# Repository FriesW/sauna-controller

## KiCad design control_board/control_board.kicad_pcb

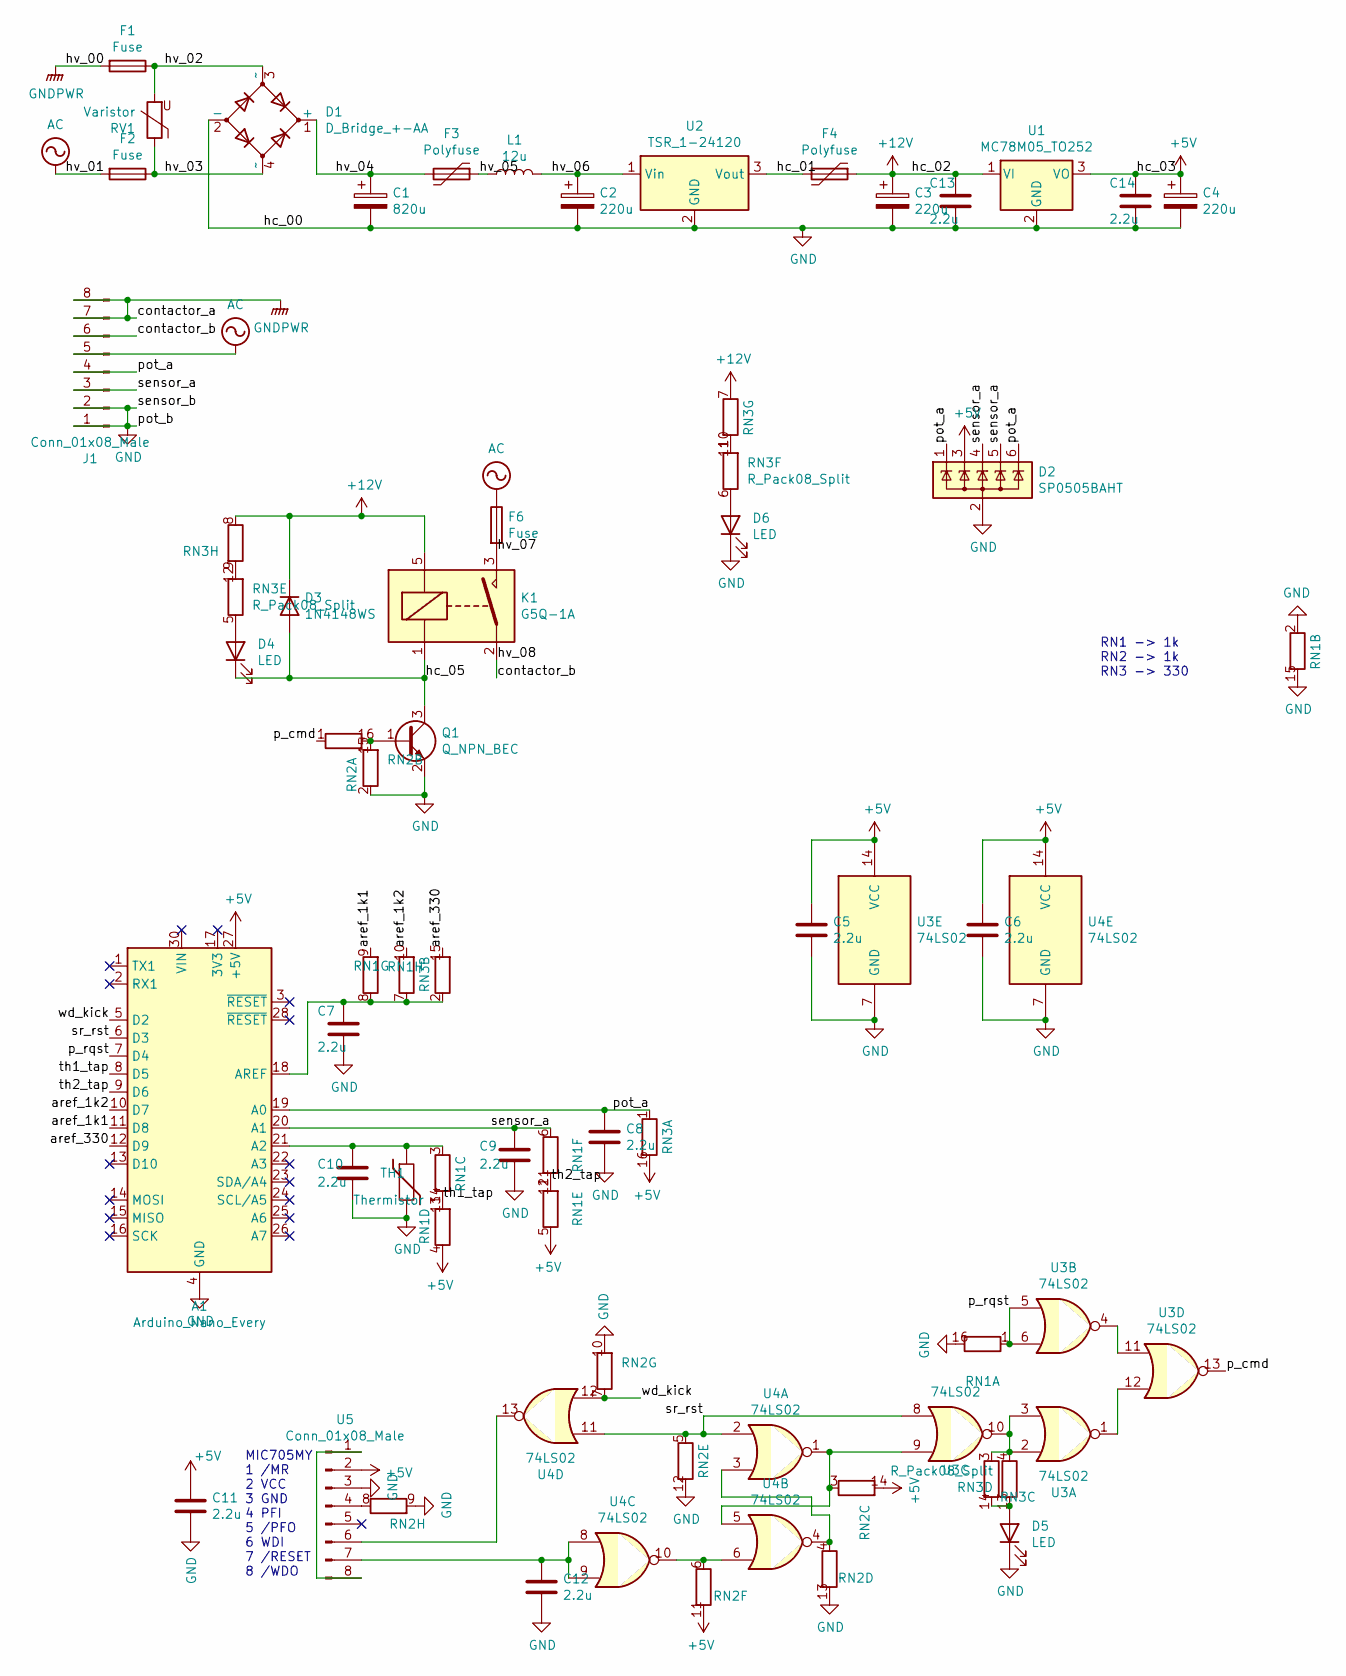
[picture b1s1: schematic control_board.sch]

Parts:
A1: Arduino_Nano_Every; Arduino_Nano
C1: 820u; CP_Elec_16x17.5
C2, C3, C4: 220u; CP_Elec_10x10
C5, C6, C7, C8, C9, C10, C11, C12, C13, C14: 2.2u; C_0805_2012Metric_Pad1.18x1.45mm_HandSolder
D1: D_Bridge_+-AA; Diode_Bridge_Diotec_ABS
D2: SP0505BAHT; SOT-23-6_Handsoldering
D3: 1N4148WS; D_SOD-323_HandSoldering
D4, D5, D6: LED; LED_0805_2012Metric_Pad1.15x1.40mm_HandSolder
F1, F2: Fuse; R_Axial_DIN0411_L9.9mm_D3.6mm_P12.70mm_Horizontal
F3, F4: Polyfuse; Fuse_2920_7451Metric_Pad2.10x5.45mm_HandSolder
F6: Fuse; Fuse_Littelfuse_395Series
J1: Conn_01x08_Male; JST_VH_B8P-VH_1x08_P3.96mm_Vertical
K1: G5Q-1A; Relay_SPDT_Omron-G5Q-1
L1: 12u; L_Abracon_ASPI-0630LR
Q1: Q_NPN_BEC; SOT-23_Handsoldering
RN1, RN2, RN3: R_Pack08_Split; SOIC-16_4.55x10.3mm_P1.27mm
RV1: Varistor; RV_Disc_D7mm_W3.6mm_P5mm
TH1: Thermistor; R_LDR_4.9x4.2mm_P2.54mm_Vertical
U1: MC78M05_TO252; TO-252-2
U2: TSR_1-24120; Converter_DCDC_RECOM_R-78B-2.0_THT
U3, U4: 74LS02; SOIC-14_3.9x8.7mm_P1.27mm
U5: Conn_01x08_Male; SOIC-8_3.9x4.9mm_P1.27mm

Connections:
+5V: A1.27 (+5V), C4.1, C5.1, C6.1, C11.1, C14.1, D2.3 (K), RN1.4 (R4.1), RN1.5 (R5.1), RN2.11 (R6.2), RN2.14 (R3.2), RN3.16 (R1.2), U1.3 (VO), U3.14 (VCC), U4.14 (VCC), U5.2
+12V: C3.1, C13.1, D3.1 (K), F4.1, K1.5, RN3.7 (R7.1), RN3.8 (R8.1), U1.1 (VI)
/aref_1k1: A1.11 (D8), RN1.9 (R8.2)
/aref_1k2: A1.10 (D7), RN1.10 (R7.2)
/aref_330: A1.12 (D9), RN3.15 (R2.2)
/contactor_b: J1.6, K1.2
/hc_01: F4.2, U2.3 (Vout)
/hc_05: D3.2 (A), D4.1 (K), K1.1, Q1.3 (C)
/hv_02: D1.3 (~~), F1.1, RV1.2
/hv_03: D1.4 (~~), F2.1, RV1.1
/hv_04: C1.1, D1.1 (+), F3.2
/hv_05: F3.1, L1.1
/hv_06: C2.1, L1.2, U2.1 (Vin)
/hv_07: F6.2, K1.3
/p_cmd: RN2.1 (R1.1), U3.13
/p_rqst: A1.7 (D4), RN1.1 (R1.1), U3.5, U3.6
/pot_a: A1.19 (A0), C8.1, D2.1 (K), D2.6 (K), J1.4, RN3.1 (R1.1)
/sensor_a: A1.20 (A1), C9.1, D2.4 (K), D2.5 (K), J1.3, RN1.6 (R6.1)
/sr_rst: A1.6 (D3), RN2.5 (R5.1), U3.8, U4.2, U4.11
/th1_tap: A1.8 (D5), RN1.13 (R4.2), RN1.14 (R3.2)
/th2_tap: A1.9 (D6), RN1.11 (R6.2), RN1.12 (R5.2)
/wd_kick: A1.5 (D2), RN2.7 (R7.1), U4.12
AC: F2.2, F6.1, J1.5
GND: A1.4 (GND), A1.29 (GND), C1.2, C2.2, C3.2, C4.2, C5.2, C6.2, C7.2, C8.2, C9.2, C10.2, C11.2, C12.2, C13.2, C14.2, D1.2 (-), D2.2 (A), D5.1 (K), D6.1 (K), J1.1, J1.2, Q1.2 (E), RN1.2 (R2.1), RN1.15 (R2.2), RN1.16 (R1.2), RN2.2 (R2.1), RN2.9 (R8.2), RN2.10 (R7.2), RN2.12 (R5.2), RN2.13 (R4.2), TH1.2, U1.2 (GND), U2.2 (GND), U3.7 (GND), U4.7 (GND), U5.3
GNDPWR: F1.2, J1.7, J1.8
unnamed: A1.18 (AREF), C7.1, RN1.7 (R7.1), RN1.8 (R8.1), RN3.2 (R2.1)
unnamed: A1.21 (A2), C10.1, RN1.3 (R3.1), TH1.1
unnamed: C12.1, U4.8, U4.9, U5.7
unnamed: D4.2 (A), RN3.5 (R5.1)
unnamed: D5.2 (A), RN3.13 (R4.2), RN3.14 (R3.2)
unnamed: D6.2 (A), RN3.6 (R6.1)
unnamed: Q1.1 (B), RN2.15 (R2.2), RN2.16 (R1.2)
unnamed: RN2.3 (R3.1), U3.9, U4.1, U4.5
unnamed: RN2.4 (R4.1), U4.3, U4.4
unnamed: RN2.6 (R6.1), U4.6, U4.10
unnamed: RN2.8 (R8.1), U5.4
unnamed: RN3.3 (R3.1), RN3.4 (R4.1), U3.2, U3.3, U3.10
unnamed: RN3.10 (R7.2), RN3.11 (R6.2)
unnamed: RN3.9 (R8.2), RN3.12 (R5.2)
unnamed: U3.1, U3.12
unnamed: U3.4, U3.11
unnamed: U4.13, U5.6
unnamed: U5.1, U5.8

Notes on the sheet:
RN1 -> 1k RN2 -> 1k RN3 -> 330
MIC705MY 1 /MR 2 VCC 3 GND 4 PFI 5 /PFO 6 WDI 7 /RESET 8 /WDO

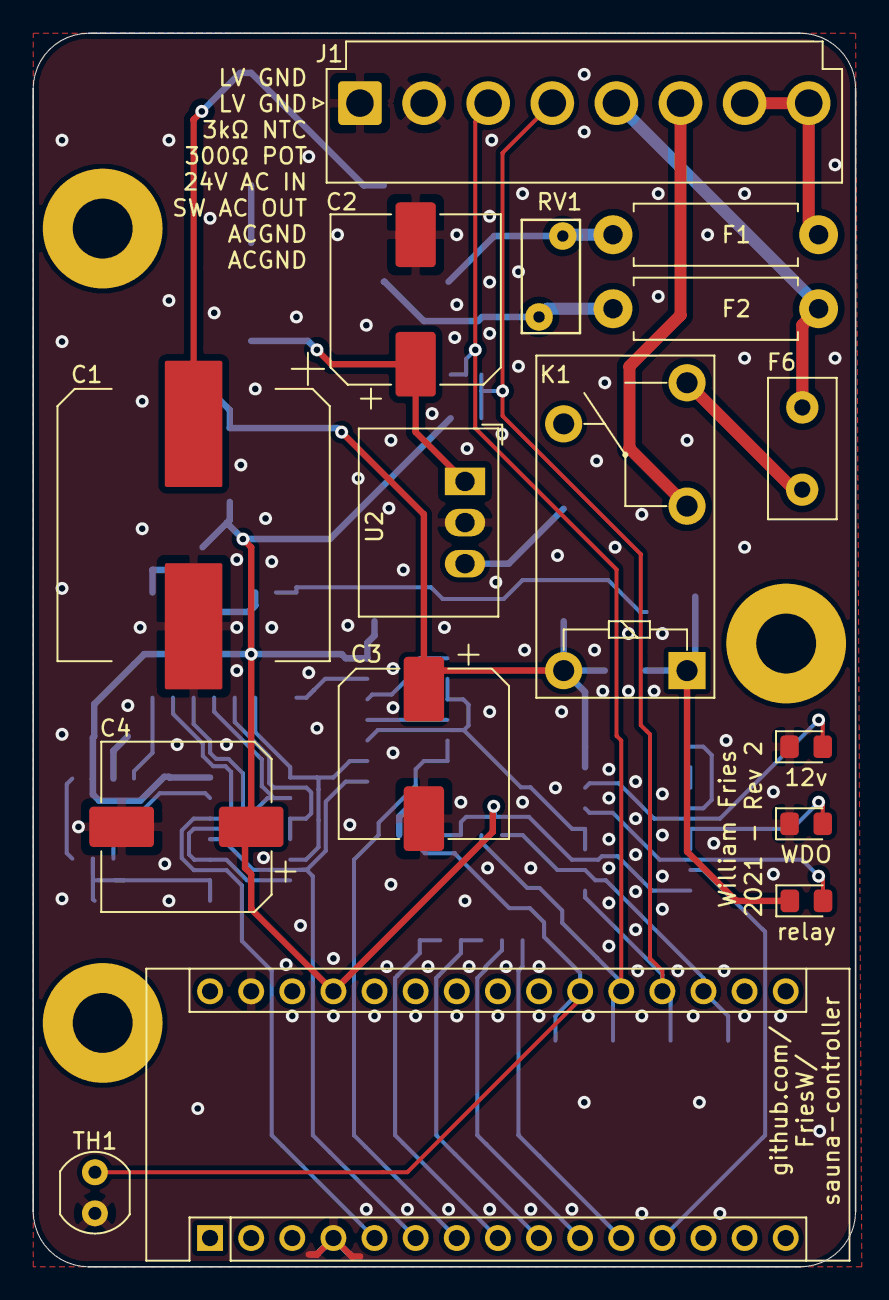
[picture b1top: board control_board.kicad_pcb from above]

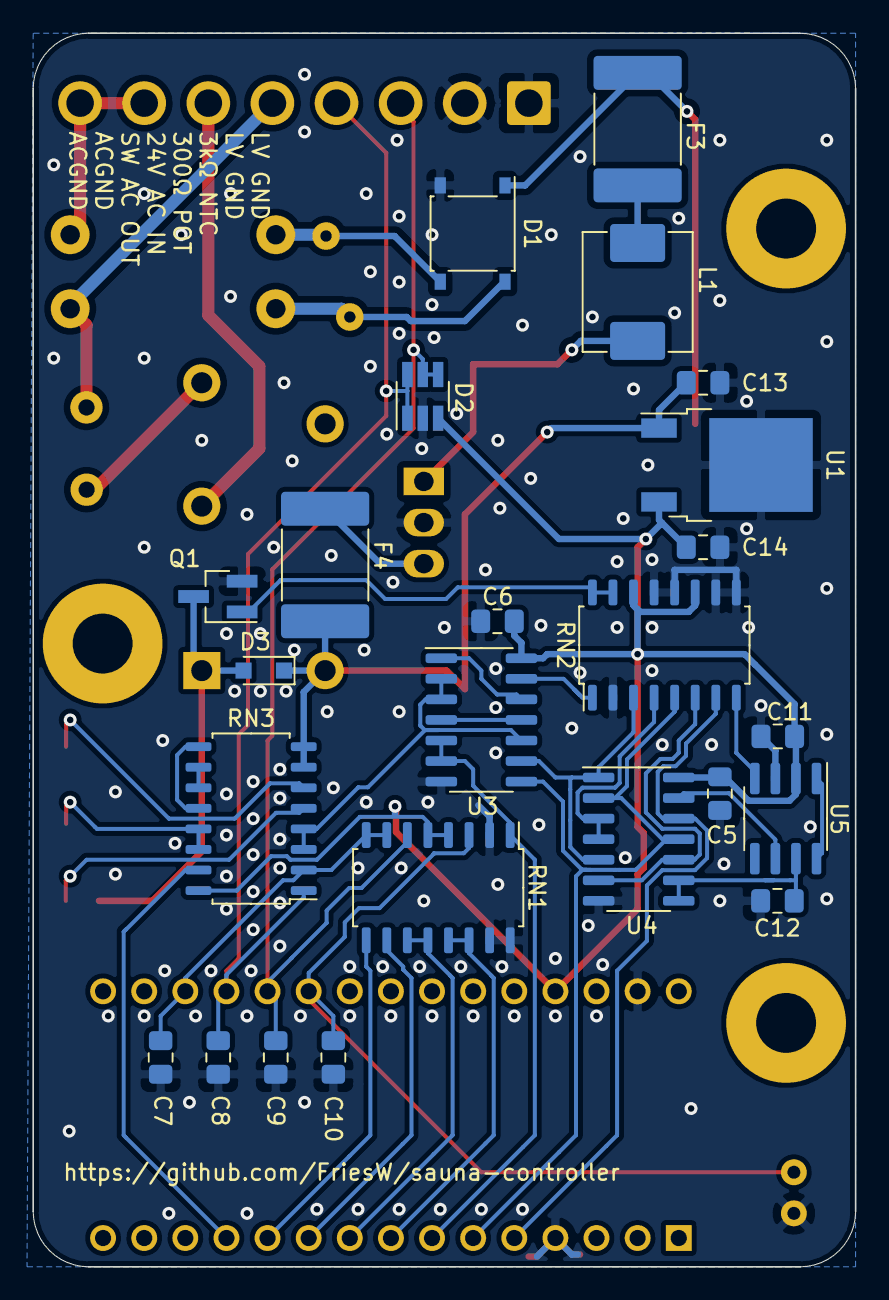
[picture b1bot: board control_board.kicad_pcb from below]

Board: 2 copper layers, 50.8 x 76.2 mm, 40 parts (24 on the bottom side), 43 nets.

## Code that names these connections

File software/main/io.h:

#ifndef _IO_H
#define _IO_H

#define P_RQST (4)
#define SR_RST (3)
#define WD_KICK (2)

#define BD_LED (13)

#define PCB_TEMP (16)
#define ROOM_TEMP (15)
#define POT (14)

#define PCB_TAP (5)
#define ROOM_TAP (6)

#define AREF_1K0 (7)
#define AREF_1K1 (8)
#define AREF_330 (9)

#endif

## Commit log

2021-01-19 Initial commit, first PCB revision
2021-01-20 Revised PCB layout
2021-01-20 Fix board perimeter and silkscreen component ids
2021-01-20 Optimize some traces
2021-01-20 Add actual mount holes
2021-01-20 Ground plane via stitching
2021-01-20 Silkscreen cleanup, DRC check, few more vias
2021-01-21 Path and fill optimization
2021-01-21 Prepare for JLCPCB
2021-01-21 Finalize design
2021-01-21 Add connector part and part search
2021-01-21 Fix some DRC errors
2021-01-21 Change LED silkscreen
2021-01-21 Export gerber
2021-01-22 Adjust mounting points
2021-01-22 Remove gerber folder
2021-01-22 New mount hole spacing, new layout
2021-01-24 Find mounting hardware
2021-01-28 BOM Updates
    Swap F1 & F2 fusable resistors to lower wattage
    Swap F6 fuse to in stock fuse, actually Littelfuse 395 series
2021-02-05 PCB revision notes
2021-02-05 SW first draft, HW test
2021-02-07 Additional testing
2021-02-08 Draft: SW decode thermistor
2021-02-08 Read analog values
2021-02-08 Add halt, implement overtemp, refactor names
2021-02-08 Prepare thermostat
2021-02-08 Refactor
2021-02-08 Thermostat: hysteresis and min cycle time
2021-02-09 Fix analog read init bug
2021-02-11 Revision notes for analog
2021-02-11 Fix compare bug, comment on AREF
2021-02-13 Spreadsheet other pot options
2021-02-13 Revise schematic and some footprints
2021-02-13 Round PCB corners
2021-02-13 Reduce width of C1 pads
2021-02-13 Draft layout
2021-02-13 Draft logic layout
2021-02-13 Layout almost done
2021-02-13 Layout complete
    TODO
    Via stitch ground
    Fix silkscreen positions
    Final check of revision notes
2021-02-13 PCB Rev2 Complete
2021-02-14 Via & trace tweaks
2021-02-14 Fix silkscreen typo
2021-02-15 Fix right edge cut
2021-06-05 Board assembly notes
2021-06-05 SW: draft AREF luts
2021-06-05 Reading ADC values
2021-06-05 Convert readings to actual resistance
2021-06-05 NTC resistence to temperature conversion
2021-06-05 Cleanup
2021-06-05 Expose final readings
2021-06-06 Candidate software
2021-06-06 Tweak values, fix thermostat addition, maintain errors instead of defaults
2021-06-06 Remove locals, cleanup logic
2021-06-06 Weighted average of readings
2021-06-06 Fix first on delay and short cycle checks in thermostat
